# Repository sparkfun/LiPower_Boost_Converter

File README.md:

LiPower - Boost Converter
========================

[
*LiPower - Boost Converter (PRT-10255)*](https://www.sparkfun.com/products/10255)

This board is based on the TPS61200 boost converter. The board is configured to work with a LiPo battery, has a
solder jumper selectable between 5V and 3.3V output, and an under voltage protection of 2.6V. 

Repository Contents
-------------------
* **/Hardware** - All Eagle design files (.brd, .sch, .STL)
* **/Production** - Test bed files and production panel files

License Information
-------------------
The hardware is released under [Creative Commons ShareAlike 4.0 International](https://creativecommons.org/licenses/by-sa/4.0/).

Distributed as-is; no warranty is given.

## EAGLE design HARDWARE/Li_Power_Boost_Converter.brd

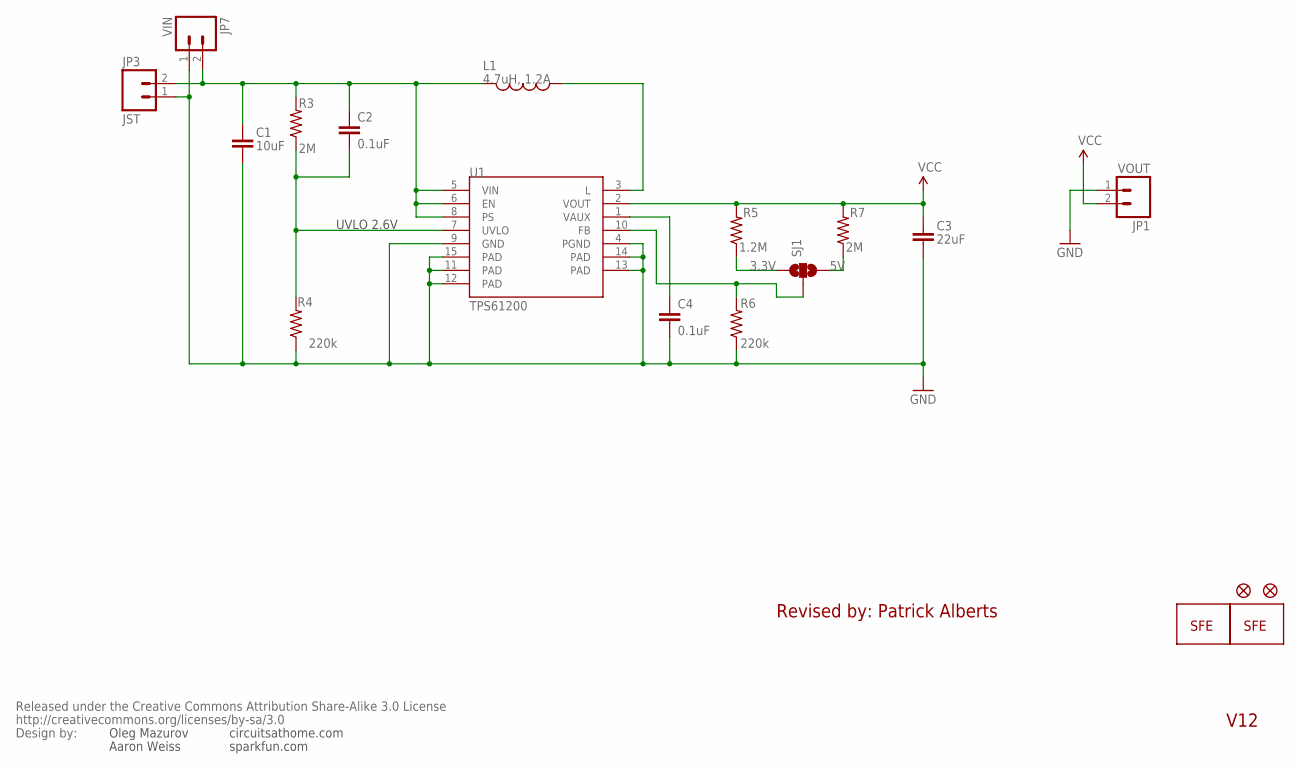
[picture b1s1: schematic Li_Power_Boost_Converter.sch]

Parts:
C1: 10uF; 1206
C2, C4: 0.1uF; 0603-CAP
C3: 22uF; 0805
JP1: VOUT; 1X02
JP2: LOGO-SFESK; SFE-LOGO-FLAME
JP3: JST; JST-2-SMD
JP4, JP5: FIDUCIAL1X2; FIDUCIAL-1X2
JP6: LOGO-SFENEW; SFE-NEW-WEBLOGO
JP7: VIN; 1X02
L1: 4.7uH, 1.2A; CDRH2D09
R3, R7: 2M; 0603-RES
R4, R6: 220k; 0603-RES
R5: 1.2M; 0603-RES
SJ1: SOLDERJUMPER_2WAYPASTE2&3; SJ_3_PASTE2&3
U1: TPS61200; QFN-10_PAD
U$1: CREATIVE_COMMONS

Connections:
3.3V: R5.1, SJ1.1
5V: R7.1, SJ1.3
FB: R6.2, SJ1.2, U1.10 (FB)
GND: C1.2, C3.2, C4.2, JP1.1, JP3.1, JP7.1, R4.1, R6.1, U1.4 (PGND), U1.9 (GND), U1.11 (PAD), U1.12 (PAD), U1.13 (PAD), U1.14 (PAD), U1.15 (PAD)
unnamed: C4.1, U1.1 (VAUX)
unnamed: L1.P$1 (1), U1.3 (L)
UVLO: C2.2, R3.1, R4.2, U1.7 (UVLO)
VCC: C3.1, JP1.2, R5.2, R7.2, U1.2 (VOUT)
VIN: C1.1, C2.1, JP3.2, JP7.2, L1.P$2 (2), R3.2, U1.5 (VIN), U1.6 (EN), U1.8 (PS)

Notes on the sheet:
UVLO 2.6V
circuitsathome.com
Oleg Mazurov
Aaron Weiss
sparkfun.com
V12
Revised by: Patrick Alberts

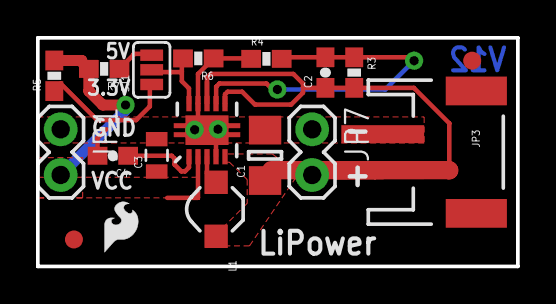
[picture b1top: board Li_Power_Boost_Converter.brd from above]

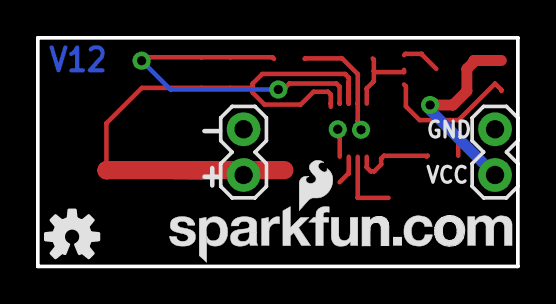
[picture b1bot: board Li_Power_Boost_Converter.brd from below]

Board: 2 copper layers, 26.7 x 12.7 mm, 21 parts (2 on the bottom side), 9 nets.

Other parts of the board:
FRAME1: FRAME-LETTER; CREATIVE_COMMONS
U$2: OSHW-LOGO-S

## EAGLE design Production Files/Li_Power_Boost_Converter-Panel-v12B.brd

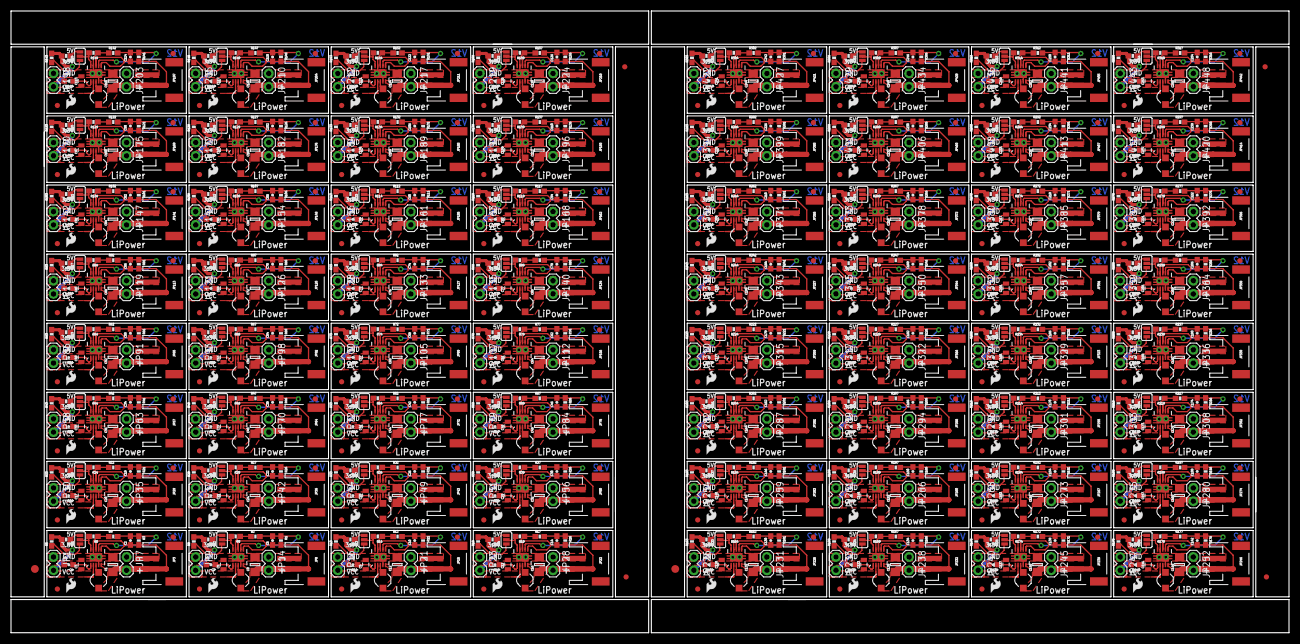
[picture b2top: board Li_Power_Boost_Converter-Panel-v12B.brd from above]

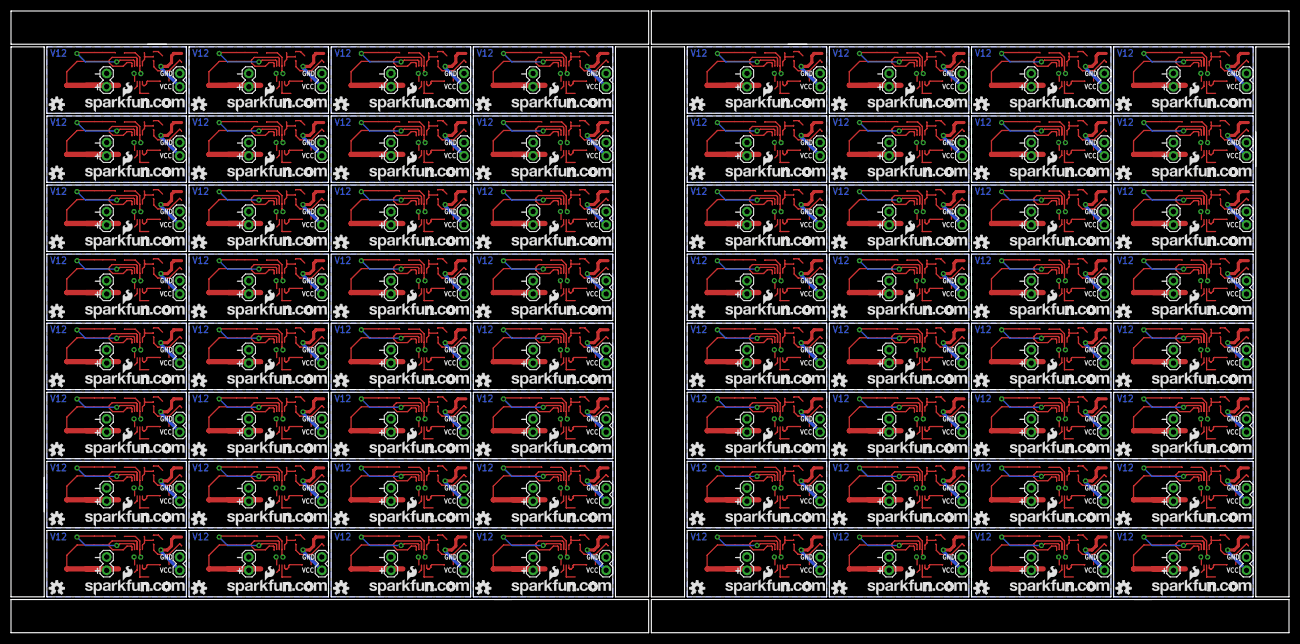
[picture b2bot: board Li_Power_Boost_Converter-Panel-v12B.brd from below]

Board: 2 copper layers, 244.3 x 118.9 mm, 1286 parts (128 on the bottom side), 576 nets.

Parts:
C1, C8, C12, C16, C20, C24, C28, C32, C36, C40, C44, C48, C52, C56, C60, C64, C68, C72, C76, C80, C84, C88, C92, C96, C100, C104, C108, C112, C116, C120, C124, C128, C132, C136, C140, C144, C148, C152, C156, C160, C164, C168, C172, C176, C180, C184, C188, C192, C196, C200, C204, C208, C212, C216, C220, C224, C228, C232, C236, C240, C244, C248, C252, C256: 10uF; 1206
C2, C4, C6, C7, C10, C11, C14, C15, C18, C19, C22, C23, C26, C27, C30, C31, C34, C35, C38, C39, C42, C43, C46, C47, C50, C51, C54, C55, C58, C59, C62, C63, C66, C67, C70, C71, C74, C75, C78, C79, C82, C83, C86, C87, C90, C91, C94, C95, C98, C99, C102, C103, C106, C107, C110, C111, C114, C115, C118, C119, C122, C123, C126, C127, C130, C131, C134, C135, C138, C139, C142, C143, C146, C147, C150, C151, C154, C155, C158, C159, C162, C163, C166, C167, C170, C171, C174, C175, C178, C179, C182, C183, C186, C187, C190, C191, C194, C195, C198, C199, C202, C203, C206, C207, C210, C211, C214, C215, C218, C219, C222, C223, C226, C227, C230, C231, C234, C235, C238, C239, C242, C243, C246, C247, C250, C251, C254, C255: 0.1uF; 0603-CAP
C3, C5, C9, C13, C17, C21, C25, C29, C33, C37, C41, C45, C49, C53, C57, C61, C65, C69, C73, C77, C81, C85, C89, C93, C97, C101, C105, C109, C113, C117, C121, C125, C129, C133, C137, C141, C145, C149, C153, C157, C161, C165, C169, C173, C177, C181, C185, C189, C193, C197, C201, C205, C209, C213, C217, C221, C225, C229, C233, C237, C241, C245, C249, C253: 22uF; 0805
E$1, E$6: FIDUCIAL-1.5X3
E$2, E$3, E$4, E$5: FIDUCIAL-1X2
JP1, JP9, JP16, JP23, JP30, JP37, JP44, JP51, JP58, JP65, JP72, JP79, JP86, JP93, JP100, JP107, JP114, JP121, JP128, JP135, JP142, JP149, JP156, JP163, JP170, JP177, JP184, JP191, JP198, JP205, JP212, JP219, JP226, JP233, JP240, JP247, JP254, JP261, JP268, JP275, JP282, JP289, JP296, JP303, JP310, JP317, JP324, JP331, JP338, JP345, JP352, JP359, JP366, JP373, JP380, JP387, JP394, JP401, JP408, JP415, JP422, JP429, JP436, JP443: VOUT; 1X02
JP2, JP10, JP17, JP24, JP31, JP38, JP45, JP52, JP59, JP66, JP73, JP80, JP87, JP94, JP101, JP108, JP115, JP122, JP129, JP136, JP143, JP150, JP157, JP164, JP171, JP178, JP185, JP192, JP199, JP206, JP213, JP220, JP227, JP234, JP241, JP248, JP255, JP262, JP269, JP276, JP283, JP290, JP297, JP304, JP311, JP318, JP325, JP332, JP339, JP346, JP353, JP360, JP367, JP374, JP381, JP388, JP395, JP402, JP409, JP416, JP423, JP430, JP437, JP444: LOGO-SFESK; SFE-LOGO-FLAME
JP3, JP8, JP15, JP22, JP29, JP36, JP43, JP50, JP57, JP64, JP71, JP78, JP85, JP92, JP99, JP106, JP113, JP120, JP127, JP134, JP141, JP148, JP155, JP162, JP169, JP176, JP183, JP190, JP197, JP204, JP211, JP218, JP225, JP232, JP239, JP246, JP253, JP260, JP267, JP274, JP281, JP288, JP295, JP302, JP309, JP316, JP323, JP330, JP337, JP344, JP351, JP358, JP365, JP372, JP379, JP386, JP393, JP400, JP407, JP414, JP421, JP428, JP435, JP442: JST; JST-2-SMD
JP4, JP5, JP11, JP12, JP18, JP19, JP25, JP26, JP32, JP33, JP39, JP40, JP46, JP47, JP53, JP54, JP60, JP61, JP67, JP68, JP74, JP75, JP81, JP82, JP88, JP89, JP95, JP96, JP102, JP103, JP109, JP110, JP116, JP117, JP123, JP124, JP130, JP131, JP137, JP138, JP144, JP145, JP151, JP152, JP158, JP159, JP165, JP166, JP172, JP173, JP179, JP180, JP186, JP187, JP193, JP194, JP200, JP201, JP207, JP208, JP214, JP215, JP221, JP222, JP228, JP229, JP235, JP236, JP242, JP243, JP249, JP250, JP256, JP257, JP263, JP264, JP270, JP271, JP277, JP278, JP284, JP285, JP291, JP292, JP298, JP299, JP305, JP306, JP312, JP313, JP319, JP320, JP326, JP327, JP333, JP334, JP340, JP341, JP347, JP348, JP354, JP355, JP361, JP362, JP368, JP369, JP375, JP376, JP382, JP383, JP389, JP390, JP396, JP397, JP403, JP404, JP410, JP411, JP417, JP418, JP424, JP425, JP431, JP432, JP438, JP439, JP445, JP446: FIDUCIAL1X2; FIDUCIAL-1X2
JP6, JP13, JP20, JP27, JP34, JP41, JP48, JP55, JP62, JP69, JP76, JP83, JP90, JP97, JP104, JP111, JP118, JP125, JP132, JP139, JP146, JP153, JP160, JP167, JP174, JP181, JP188, JP195, JP202, JP209, JP216, JP223, JP230, JP237, JP244, JP251, JP258, JP265, JP272, JP279, JP286, JP293, JP300, JP307, JP314, JP321, JP328, JP335, JP342, JP349, JP356, JP363, JP370, JP377, JP384, JP391, JP398, JP405, JP412, JP419, JP426, JP433, JP440, JP447: LOGO-SFENEW; SFE-NEW-WEBLOGO
JP7, JP14, JP21, JP28, JP35, JP42, JP49, JP56, JP63, JP70, JP77, JP84, JP91, JP98, JP105, JP112, JP119, JP126, JP133, JP140, JP147, JP154, JP161, JP168, JP175, JP182, JP189, JP196, JP203, JP210, JP217, JP224, JP231, JP238, JP245, JP252, JP259, JP266, JP273, JP280, JP287, JP294, JP301, JP308, JP315, JP322, JP329, JP336, JP343, JP350, JP357, JP364, JP371, JP378, JP385, JP392, JP399, JP406, JP413, JP420, JP427, JP434, JP441, JP448: VIN; 1X02
L1, L2, L3, L4, L5, L6, L7, L8, L9, L10, L11, L12, L13, L14, L15, L16, L17, L18, L19, L20, L21, L22, L23, L24, L25, L26, L27, L28, L29, L30, L31, L32, L33, L34, L35, L36, L37, L38, L39, L40, L41, L42, L43, L44, L45, L46, L47, L48, L49, L50, L51, L52, L53, L54, L55, L56, L57, L58, L59, L60, L61, L62, L63, L64: 4.7uH, 1.2A; CDRH2D09
R1, R3, R7, R10, R11, R15, R16, R20, R21, R25, R26, R30, R31, R35, R36, R40, R41, R45, R46, R50, R51, R55, R56, R60, R61, R65, R66, R70, R71, R75, R76, R80, R81, R85, R86, R90, R91, R95, R96, R100, R101, R105, R106, R110, R111, R115, R116, R120, R121, R125, R126, R130, R131, R135, R136, R140, R141, R145, R146, R150, R151, R155, R156, R160, R161, R165, R166, R170, R171, R175, R176, R180, R181, R185, R186, R190, R191, R195, R196, R200, R201, R205, R206, R210, R211, R215, R216, R220, R221, R225, R226, R230, R231, R235, R236, R240, R241, R245, R246, R250, R251, R255, R256, R260, R261, R265, R266, R270, R271, R275, R276, R280, R281, R285, R286, R290, R291, R295, R296, R300, R301, R305, R306, R310, R311, R315, R316, R320: 2M; 0603-RES
R2, R4, R6, R9, R12, R14, R17, R19, R22, R24, R27, R29, R32, R34, R37, R39, R42, R44, R47, R49, R52, R54, R57, R59, R62, R64, R67, R69, R72, R74, R77, R79, R82, R84, R87, R89, R92, R94, R97, R99, R102, R104, R107, R109, R112, R114, R117, R119, R122, R124, R127, R129, R132, R134, R137, R139, R142, R144, R147, R149, R152, R154, R157, R159, R162, R164, R167, R169, R172, R174, R177, R179, R182, R184, R187, R189, R192, R194, R197, R199, R202, R204, R207, R209, R212, R214, R217, R219, R222, R224, R227, R229, R232, R234, R237, R239, R242, R244, R247, R249, R252, R254, R257, R259, R262, R264, R267, R269, R272, R274, R277, R279, R282, R284, R287, R289, R292, R294, R297, R299, R302, R304, R307, R309, R312, R314, R317, R319: 220k; 0603-RES
R5, R8, R13, R18, R23, R28, R33, R38, R43, R48, R53, R58, R63, R68, R73, R78, R83, R88, R93, R98, R103, R108, R113, R118, R123, R128, R133, R138, R143, R148, R153, R158, R163, R168, R173, R178, R183, R188, R193, R198, R203, R208, R213, R218, R223, R228, R233, R238, R243, R248, R253, R258, R263, R268, R273, R278, R283, R288, R293, R298, R303, R308, R313, R318: 1.2M; 0603-RES
SJ1, SJ2, SJ3, SJ4, SJ5, SJ6, SJ7, SJ8, SJ9, SJ10, SJ11, SJ12, SJ13, SJ14, SJ15, SJ16, SJ17, SJ18, SJ19, SJ20, SJ21, SJ22, SJ23, SJ24, SJ25, SJ26, SJ27, SJ28, SJ29, SJ30, SJ31, SJ32, SJ33, SJ34, SJ35, SJ36, SJ37, SJ38, SJ39, SJ40, SJ41, SJ42, SJ43, SJ44, SJ45, SJ46, SJ47, SJ48, SJ49, SJ50, SJ51, SJ52, SJ53, SJ54, SJ55, SJ56, SJ57, SJ58, SJ59, SJ60, SJ61, SJ62, SJ63, SJ64: SJ_3_PASTE2&3
U1, U2, U3, U4, U5, U6, U7, U8, U9, U10, U11, U12, U13, U14, U15, U16, U17, U18, U19, U20, U21, U22, U23, U24, U25, U26, U27, U28, U29, U30, U31, U32, U33, U34, U35, U36, U37, U38, U39, U40, U41, U42, U43, U44, U45, U46, U47, U48, U49, U50, U51, U52, U53, U54, U55, U56, U57, U58, U59, U60, U61, U62, U63, U64: TPS61200; QFN-10_PAD
U$1, U$2, U$3, U$4, U$5, U$6, U$7, U$8, U$9, U$10, U$11, U$12, U$13, U$14, U$15, U$16, U$17, U$18, U$19, U$20, U$21, U$22, U$23, U$24, U$25, U$26, U$27, U$28, U$29, U$30, U$31, U$32, U$33, U$34, U$35, U$36, U$37, U$38, U$39, U$40, U$41, U$42, U$43, U$44, U$45, U$46, U$47, U$48, U$49, U$50, U$51, U$52, U$53, U$54, U$55, U$56, U$57, U$58, U$59, U$60, U$61, U$62, U$63, U$64: OSHW-LOGO-S

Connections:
3.3V: R5.1, SJ1.1
3.3V1: R8.1, SJ2.1
3.3V2: R13.1, SJ3.1
3.3V3: R18.1, SJ4.1
3.3V4: R23.1, SJ5.1
3.3V5: R28.1, SJ6.1
3.3V6: R33.1, SJ7.1
3.3V7: R38.1, SJ8.1
3.3V8: R43.1, SJ9.1
3.3V9: R48.1, SJ10.1
3.3V10: R53.1, SJ11.1
3.3V11: R58.1, SJ12.1
3.3V12: R63.1, SJ13.1
3.3V13: R68.1, SJ14.1
3.3V14: R73.1, SJ15.1
3.3V15: R78.1, SJ16.1
3.3V16: R83.1, SJ17.1
3.3V17: R88.1, SJ18.1
3.3V18: R93.1, SJ19.1
3.3V19: R98.1, SJ20.1
3.3V20: R103.1, SJ21.1
3.3V21: R108.1, SJ22.1
3.3V22: R113.1, SJ23.1
3.3V23: R118.1, SJ24.1
3.3V24: R123.1, SJ25.1
3.3V25: R128.1, SJ26.1
3.3V26: R133.1, SJ27.1
3.3V27: R138.1, SJ28.1
3.3V28: R143.1, SJ29.1
3.3V29: R148.1, SJ30.1
3.3V30: R153.1, SJ31.1
3.3V31: R158.1, SJ32.1
3.3V32: R163.1, SJ33.1
3.3V33: R168.1, SJ34.1
3.3V34: R173.1, SJ35.1
3.3V35: R178.1, SJ36.1
3.3V36: R183.1, SJ37.1
3.3V37: R188.1, SJ38.1
3.3V38: R193.1, SJ39.1
3.3V39: R198.1, SJ40.1
3.3V40: R203.1, SJ41.1
3.3V41: R208.1, SJ42.1
3.3V42: R213.1, SJ43.1
3.3V43: R218.1, SJ44.1
3.3V44: R223.1, SJ45.1
3.3V45: R228.1, SJ46.1
3.3V46: R233.1, SJ47.1
3.3V47: R238.1, SJ48.1
3.3V48: R243.1, SJ49.1
3.3V49: R248.1, SJ50.1
3.3V50: R253.1, SJ51.1
3.3V51: R258.1, SJ52.1
3.3V52: R263.1, SJ53.1
3.3V53: R268.1, SJ54.1
3.3V54: R273.1, SJ55.1
3.3V55: R278.1, SJ56.1
3.3V56: R283.1, SJ57.1
3.3V57: R288.1, SJ58.1
3.3V58: R293.1, SJ59.1
3.3V59: R298.1, SJ60.1
3.3V60: R303.1, SJ61.1
3.3V61: R308.1, SJ62.1
3.3V62: R313.1, SJ63.1
3.3V63: R318.1, SJ64.1
5V: R7.1, SJ1.3
5V1: R10.1, SJ2.3
5V2: R15.1, SJ3.3
5V3: R20.1, SJ4.3
5V4: R25.1, SJ5.3
5V5: R30.1, SJ6.3
5V6: R35.1, SJ7.3
5V7: R40.1, SJ8.3
5V8: R45.1, SJ9.3
5V9: R50.1, SJ10.3
5V10: R55.1, SJ11.3
5V11: R60.1, SJ12.3
5V12: R65.1, SJ13.3
5V13: R70.1, SJ14.3
5V14: R75.1, SJ15.3
5V15: R80.1, SJ16.3
5V16: R85.1, SJ17.3
5V17: R90.1, SJ18.3
5V18: R95.1, SJ19.3
5V19: R100.1, SJ20.3
5V20: R105.1, SJ21.3
5V21: R110.1, SJ22.3
5V22: R115.1, SJ23.3
5V23: R120.1, SJ24.3
5V24: R125.1, SJ25.3
5V25: R130.1, SJ26.3
5V26: R135.1, SJ27.3
5V27: R140.1, SJ28.3
5V28: R145.1, SJ29.3
5V29: R150.1, SJ30.3
5V30: R155.1, SJ31.3
5V31: R160.1, SJ32.3
5V32: R165.1, SJ33.3
5V33: R170.1, SJ34.3
5V34: R175.1, SJ35.3
5V35: R180.1, SJ36.3
5V36: R185.1, SJ37.3
5V37: R190.1, SJ38.3
5V38: R195.1, SJ39.3
5V39: R200.1, SJ40.3
5V40: R205.1, SJ41.3
5V41: R210.1, SJ42.3
5V42: R215.1, SJ43.3
5V43: R220.1, SJ44.3
5V44: R225.1, SJ45.3
5V45: R230.1, SJ46.3
5V46: R235.1, SJ47.3
5V47: R240.1, SJ48.3
5V48: R245.1, SJ49.3
5V49: R250.1, SJ50.3
5V50: R255.1, SJ51.3
5V51: R260.1, SJ52.3
5V52: R265.1, SJ53.3
5V53: R270.1, SJ54.3
5V54: R275.1, SJ55.3
5V55: R280.1, SJ56.3
5V56: R285.1, SJ57.3
5V57: R290.1, SJ58.3
5V58: R295.1, SJ59.3
5V59: R300.1, SJ60.3
5V60: R305.1, SJ61.3
5V61: R310.1, SJ62.3
5V62: R315.1, SJ63.3
5V63: R320.1, SJ64.3
FB: R6.2, SJ1.2, U1.10
FB1: R9.2, SJ2.2, U2.10
FB2: R14.2, SJ3.2, U3.10
FB3: R19.2, SJ4.2, U4.10
FB4: R24.2, SJ5.2, U5.10
FB5: R29.2, SJ6.2, U6.10
FB6: R34.2, SJ7.2, U7.10
FB7: R39.2, SJ8.2, U8.10
FB8: R44.2, SJ9.2, U9.10
FB9: R49.2, SJ10.2, U10.10
FB10: R54.2, SJ11.2, U11.10
FB11: R59.2, SJ12.2, U12.10
FB12: R64.2, SJ13.2, U13.10
FB13: R69.2, SJ14.2, U14.10
FB14: R74.2, SJ15.2, U15.10
FB15: R79.2, SJ16.2, U16.10
FB16: R84.2, SJ17.2, U17.10
FB17: R89.2, SJ18.2, U18.10
FB18: R94.2, SJ19.2, U19.10
FB19: R99.2, SJ20.2, U20.10
FB20: R104.2, SJ21.2, U21.10
FB21: R109.2, SJ22.2, U22.10
FB22: R114.2, SJ23.2, U23.10
FB23: R119.2, SJ24.2, U24.10
FB24: R124.2, SJ25.2, U25.10
FB25: R129.2, SJ26.2, U26.10
FB26: R134.2, SJ27.2, U27.10
FB27: R139.2, SJ28.2, U28.10
FB28: R144.2, SJ29.2, U29.10
FB29: R149.2, SJ30.2, U30.10
FB30: R154.2, SJ31.2, U31.10
FB31: R159.2, SJ32.2, U32.10
FB32: R164.2, SJ33.2, U33.10
FB33: R169.2, SJ34.2, U34.10
FB34: R174.2, SJ35.2, U35.10
FB35: R179.2, SJ36.2, U36.10
FB36: R184.2, SJ37.2, U37.10
FB37: R189.2, SJ38.2, U38.10
FB38: R194.2, SJ39.2, U39.10
FB39: R199.2, SJ40.2, U40.10
FB40: R204.2, SJ41.2, U41.10
FB41: R209.2, SJ42.2, U42.10
FB42: R214.2, SJ43.2, U43.10
FB43: R219.2, SJ44.2, U44.10
FB44: R224.2, SJ45.2, U45.10
FB45: R229.2, SJ46.2, U46.10
FB46: R234.2, SJ47.2, U47.10
FB47: R239.2, SJ48.2, U48.10
FB48: R244.2, SJ49.2, U49.10
FB49: R249.2, SJ50.2, U50.10
FB50: R254.2, SJ51.2, U51.10
FB51: R259.2, SJ52.2, U52.10
FB52: R264.2, SJ53.2, U53.10
FB53: R269.2, SJ54.2, U54.10
FB54: R274.2, SJ55.2, U55.10
FB55: R279.2, SJ56.2, U56.10
FB56: R284.2, SJ57.2, U57.10
FB57: R289.2, SJ58.2, U58.10
FB58: R294.2, SJ59.2, U59.10
FB59: R299.2, SJ60.2, U60.10
FB60: R304.2, SJ61.2, U61.10
FB61: R309.2, SJ62.2, U62.10
FB62: R314.2, SJ63.2, U63.10
FB63: R319.2, SJ64.2, U64.10
GND: C1.2, C3.2, C4.2, JP1.1, JP3.1, JP7.1, R4.1, R6.1, U1.4, U1.9, U1.11, U1.12, U1.13, U1.14, U1.15
GND1: C5.2, C7.2, C8.2, JP8.1, JP9.1, JP14.1, R2.1, R9.1, U2.4, U2.9, U2.11, U2.12, U2.13, U2.14, U2.15
GND2: C9.2, C11.2, C12.2, JP15.1, JP16.1, JP21.1, R12.1, R14.1, U3.4, U3.9, U3.11, U3.12, U3.13, U3.14, U3.15
GND3: C13.2, C15.2, C16.2, JP22.1, JP23.1, JP28.1, R17.1, R19.1, U4.4, U4.9, U4.11, U4.12, U4.13, U4.14, U4.15
GND4: C17.2, C19.2, C20.2, JP29.1, JP30.1, JP35.1, R22.1, R24.1, U5.4, U5.9, U5.11, U5.12, U5.13, U5.14, U5.15
GND5: C21.2, C23.2, C24.2, JP36.1, JP37.1, JP42.1, R27.1, R29.1, U6.4, U6.9, U6.11, U6.12, U6.13, U6.14, U6.15
GND6: C25.2, C27.2, C28.2, JP43.1, JP44.1, JP49.1, R32.1, R34.1, U7.4, U7.9, U7.11, U7.12, U7.13, U7.14, U7.15
GND7: C29.2, C31.2, C32.2, JP50.1, JP51.1, JP56.1, R37.1, R39.1, U8.4, U8.9, U8.11, U8.12, U8.13, U8.14, U8.15
GND8: C33.2, C35.2, C36.2, JP57.1, JP58.1, JP63.1, R42.1, R44.1, U9.4, U9.9, U9.11, U9.12, U9.13, U9.14, U9.15
GND9: C37.2, C39.2, C40.2, JP64.1, JP65.1, JP70.1, R47.1, R49.1, U10.4, U10.9, U10.11, U10.12, U10.13, U10.14, U10.15
GND10: C41.2, C43.2, C44.2, JP71.1, JP72.1, JP77.1, R52.1, R54.1, U11.4, U11.9, U11.11, U11.12, U11.13, U11.14, U11.15
GND11: C45.2, C47.2, C48.2, JP78.1, JP79.1, JP84.1, R57.1, R59.1, U12.4, U12.9, U12.11, U12.12, U12.13, U12.14, U12.15
GND12: C49.2, C51.2, C52.2, JP85.1, JP86.1, JP91.1, R62.1, R64.1, U13.4, U13.9, U13.11, U13.12, U13.13, U13.14, U13.15
GND13: C53.2, C55.2, C56.2, JP92.1, JP93.1, JP98.1, R67.1, R69.1, U14.4, U14.9, U14.11, U14.12, U14.13, U14.14, U14.15
GND14: C57.2, C59.2, C60.2, JP99.1, JP100.1, JP105.1, R72.1, R74.1, U15.4, U15.9, U15.11, U15.12, U15.13, U15.14, U15.15
GND15: C61.2, C63.2, C64.2, JP106.1, JP107.1, JP112.1, R77.1, R79.1, U16.4, U16.9, U16.11, U16.12, U16.13, U16.14, U16.15
GND16: C65.2, C67.2, C68.2, JP113.1, JP114.1, JP119.1, R82.1, R84.1, U17.4, U17.9, U17.11, U17.12, U17.13, U17.14, U17.15
GND17: C69.2, C71.2, C72.2, JP120.1, JP121.1, JP126.1, R87.1, R89.1, U18.4, U18.9, U18.11, U18.12, U18.13, U18.14, U18.15
GND18: C73.2, C75.2, C76.2, JP127.1, JP128.1, JP133.1, R92.1, R94.1, U19.4, U19.9, U19.11, U19.12, U19.13, U19.14, U19.15
GND19: C77.2, C79.2, C80.2, JP134.1, JP135.1, JP140.1, R97.1, R99.1, U20.4, U20.9, U20.11, U20.12, U20.13, U20.14, U20.15
GND20: C81.2, C83.2, C84.2, JP141.1, JP142.1, JP147.1, R102.1, R104.1, U21.4, U21.9, U21.11, U21.12, U21.13, U21.14, U21.15
GND21: C85.2, C87.2, C88.2, JP148.1, JP149.1, JP154.1, R107.1, R109.1, U22.4, U22.9, U22.11, U22.12, U22.13, U22.14, U22.15
GND22: C89.2, C91.2, C92.2, JP155.1, JP156.1, JP161.1, R112.1, R114.1, U23.4, U23.9, U23.11, U23.12, U23.13, U23.14, U23.15
GND23: C93.2, C95.2, C96.2, JP162.1, JP163.1, JP168.1, R117.1, R119.1, U24.4, U24.9, U24.11, U24.12, U24.13, U24.14, U24.15
GND24: C97.2, C99.2, C100.2, JP169.1, JP170.1, JP175.1, R122.1, R124.1, U25.4, U25.9, U25.11, U25.12, U25.13, U25.14, U25.15
GND25: C101.2, C103.2, C104.2, JP176.1, JP177.1, JP182.1, R127.1, R129.1, U26.4, U26.9, U26.11, U26.12, U26.13, U26.14, U26.15
GND26: C105.2, C107.2, C108.2, JP183.1, JP184.1, JP189.1, R132.1, R134.1, U27.4, U27.9, U27.11, U27.12, U27.13, U27.14, U27.15
GND27: C109.2, C111.2, C112.2, JP190.1, JP191.1, JP196.1, R137.1, R139.1, U28.4, U28.9, U28.11, U28.12, U28.13, U28.14, U28.15
GND28: C113.2, C115.2, C116.2, JP197.1, JP198.1, JP203.1, R142.1, R144.1, U29.4, U29.9, U29.11, U29.12, U29.13, U29.14, U29.15
GND29: C117.2, C119.2, C120.2, JP204.1, JP205.1, JP210.1, R147.1, R149.1, U30.4, U30.9, U30.11, U30.12, U30.13, U30.14, U30.15
GND30: C121.2, C123.2, C124.2, JP211.1, JP212.1, JP217.1, R152.1, R154.1, U31.4, U31.9, U31.11, U31.12, U31.13, U31.14, U31.15
GND31: C125.2, C127.2, C128.2, JP218.1, JP219.1, JP224.1, R157.1, R159.1, U32.4, U32.9, U32.11, U32.12, U32.13, U32.14, U32.15
GND32: C129.2, C131.2, C132.2, JP225.1, JP226.1, JP231.1, R162.1, R164.1, U33.4, U33.9, U33.11, U33.12, U33.13, U33.14, U33.15
GND33: C133.2, C135.2, C136.2, JP232.1, JP233.1, JP238.1, R167.1, R169.1, U34.4, U34.9, U34.11, U34.12, U34.13, U34.14, U34.15
GND34: C137.2, C139.2, C140.2, JP239.1, JP240.1, JP245.1, R172.1, R174.1, U35.4, U35.9, U35.11, U35.12, U35.13, U35.14, U35.15
GND35: C141.2, C143.2, C144.2, JP246.1, JP247.1, JP252.1, R177.1, R179.1, U36.4, U36.9, U36.11, U36.12, U36.13, U36.14, U36.15
GND36: C145.2, C147.2, C148.2, JP253.1, JP254.1, JP259.1, R182.1, R184.1, U37.4, U37.9, U37.11, U37.12, U37.13, U37.14, U37.15
GND37: C149.2, C151.2, C152.2, JP260.1, JP261.1, JP266.1, R187.1, R189.1, U38.4, U38.9, U38.11, U38.12, U38.13, U38.14, U38.15
GND38: C153.2, C155.2, C156.2, JP267.1, JP268.1, JP273.1, R192.1, R194.1, U39.4, U39.9, U39.11, U39.12, U39.13, U39.14, U39.15
GND39: C157.2, C159.2, C160.2, JP274.1, JP275.1, JP280.1, R197.1, R199.1, U40.4, U40.9, U40.11, U40.12, U40.13, U40.14, U40.15
GND40: C161.2, C163.2, C164.2, JP281.1, JP282.1, JP287.1, R202.1, R204.1, U41.4, U41.9, U41.11, U41.12, U41.13, U41.14, U41.15
GND41: C165.2, C167.2, C168.2, JP288.1, JP289.1, JP294.1, R207.1, R209.1, U42.4, U42.9, U42.11, U42.12, U42.13, U42.14, U42.15
GND42: C169.2, C171.2, C172.2, JP295.1, JP296.1, JP301.1, R212.1, R214.1, U43.4, U43.9, U43.11, U43.12, U43.13, U43.14, U43.15
GND43: C173.2, C175.2, C176.2, JP302.1, JP303.1, JP308.1, R217.1, R219.1, U44.4, U44.9, U44.11, U44.12, U44.13, U44.14, U44.15
GND44: C177.2, C179.2, C180.2, JP309.1, JP310.1, JP315.1, R222.1, R224.1, U45.4, U45.9, U45.11, U45.12, U45.13, U45.14, U45.15
GND45: C181.2, C183.2, C184.2, JP316.1, JP317.1, JP322.1, R227.1, R229.1, U46.4, U46.9, U46.11, U46.12, U46.13, U46.14, U46.15
GND46: C185.2, C187.2, C188.2, JP323.1, JP324.1, JP329.1, R232.1, R234.1, U47.4, U47.9, U47.11, U47.12, U47.13, U47.14, U47.15
GND47: C189.2, C191.2, C192.2, JP330.1, JP331.1, JP336.1, R237.1, R239.1, U48.4, U48.9, U48.11, U48.12, U48.13, U48.14, U48.15
GND48: C193.2, C195.2, C196.2, JP337.1, JP338.1, JP343.1, R242.1, R244.1, U49.4, U49.9, U49.11, U49.12, U49.13, U49.14, U49.15
GND49: C197.2, C199.2, C200.2, JP344.1, JP345.1, JP350.1, R247.1, R249.1, U50.4, U50.9, U50.11, U50.12, U50.13, U50.14, U50.15
GND50: C201.2, C203.2, C204.2, JP351.1, JP352.1, JP357.1, R252.1, R254.1, U51.4, U51.9, U51.11, U51.12, U51.13, U51.14, U51.15
GND51: C205.2, C207.2, C208.2, JP358.1, JP359.1, JP364.1, R257.1, R259.1, U52.4, U52.9, U52.11, U52.12, U52.13, U52.14, U52.15
GND52: C209.2, C211.2, C212.2, JP365.1, JP366.1, JP371.1, R262.1, R264.1, U53.4, U53.9, U53.11, U53.12, U53.13, U53.14, U53.15
GND53: C213.2, C215.2, C216.2, JP372.1, JP373.1, JP378.1, R267.1, R269.1, U54.4, U54.9, U54.11, U54.12, U54.13, U54.14, U54.15
GND54: C217.2, C219.2, C220.2, JP379.1, JP380.1, JP385.1, R272.1, R274.1, U55.4, U55.9, U55.11, U55.12, U55.13, U55.14, U55.15
GND55: C221.2, C223.2, C224.2, JP386.1, JP387.1, JP392.1, R277.1, R279.1, U56.4, U56.9, U56.11, U56.12, U56.13, U56.14, U56.15
GND56: C225.2, C227.2, C228.2, JP393.1, JP394.1, JP399.1, R282.1, R284.1, U57.4, U57.9, U57.11, U57.12, U57.13, U57.14, U57.15
GND57: C229.2, C231.2, C232.2, JP400.1, JP401.1, JP406.1, R287.1, R289.1, U58.4, U58.9, U58.11, U58.12, U58.13, U58.14, U58.15
GND58: C233.2, C235.2, C236.2, JP407.1, JP408.1, JP413.1, R292.1, R294.1, U59.4, U59.9, U59.11, U59.12, U59.13, U59.14, U59.15
GND59: C237.2, C239.2, C240.2, JP414.1, JP415.1, JP420.1, R297.1, R299.1, U60.4, U60.9, U60.11, U60.12, U60.13, U60.14, U60.15
GND60: C241.2, C243.2, C244.2, JP421.1, JP422.1, JP427.1, R302.1, R304.1, U61.4, U61.9, U61.11, U61.12, U61.13, U61.14, U61.15
GND61: C245.2, C247.2, C248.2, JP428.1, JP429.1, JP434.1, R307.1, R309.1, U62.4, U62.9, U62.11, U62.12, U62.13, U62.14, U62.15
GND62: C249.2, C251.2, C252.2, JP435.1, JP436.1, JP441.1, R312.1, R314.1, U63.4, U63.9, U63.11, U63.12, U63.13, U63.14, U63.15
GND63: C253.2, C255.2, C256.2, JP442.1, JP443.1, JP448.1, R317.1, R319.1, U64.4, U64.9, U64.11, U64.12, U64.13, U64.14, U64.15
unnamed: C4.1, U1.1
unnamed: L1.P$1, U1.3
unnamed: L2.P$1, U2.3
unnamed: C7.1, U2.1
unnamed: L3.P$1, U3.3
unnamed: C11.1, U3.1
unnamed: L4.P$1, U4.3
unnamed: C15.1, U4.1
unnamed: L5.P$1, U5.3
unnamed: C19.1, U5.1
unnamed: L6.P$1, U6.3
unnamed: C23.1, U6.1
unnamed: L7.P$1, U7.3
unnamed: C27.1, U7.1
unnamed: L8.P$1, U8.3
unnamed: C31.1, U8.1
unnamed: L9.P$1, U9.3
unnamed: C35.1, U9.1
unnamed: L10.P$1, U10.3
unnamed: C39.1, U10.1
unnamed: L11.P$1, U11.3
unnamed: C43.1, U11.1
unnamed: L12.P$1, U12.3
unnamed: C47.1, U12.1
unnamed: L13.P$1, U13.3
unnamed: C51.1, U13.1
unnamed: L14.P$1, U14.3
unnamed: C55.1, U14.1
unnamed: L15.P$1, U15.3
unnamed: C59.1, U15.1
unnamed: L16.P$1, U16.3
unnamed: C63.1, U16.1
unnamed: L17.P$1, U17.3
unnamed: C67.1, U17.1
unnamed: L18.P$1, U18.3
unnamed: C71.1, U18.1
unnamed: L19.P$1, U19.3
unnamed: C75.1, U19.1
unnamed: L20.P$1, U20.3
unnamed: C79.1, U20.1
unnamed: L21.P$1, U21.3
unnamed: C83.1, U21.1
unnamed: L22.P$1, U22.3
unnamed: C87.1, U22.1
unnamed: L23.P$1, U23.3
unnamed: C91.1, U23.1
unnamed: L24.P$1, U24.3
unnamed: C95.1, U24.1
unnamed: L25.P$1, U25.3
unnamed: C99.1, U25.1
unnamed: L26.P$1, U26.3
unnamed: C103.1, U26.1
unnamed: L27.P$1, U27.3
unnamed: C107.1, U27.1
unnamed: L28.P$1, U28.3
unnamed: C111.1, U28.1
unnamed: L29.P$1, U29.3
unnamed: C115.1, U29.1
unnamed: L30.P$1, U30.3
unnamed: C119.1, U30.1
unnamed: L31.P$1, U31.3
unnamed: C123.1, U31.1
unnamed: L32.P$1, U32.3
unnamed: C127.1, U32.1
unnamed: L33.P$1, U33.3
unnamed: C131.1, U33.1
unnamed: L34.P$1, U34.3
unnamed: C135.1, U34.1
unnamed: L35.P$1, U35.3
unnamed: C139.1, U35.1
unnamed: L36.P$1, U36.3
unnamed: C143.1, U36.1
unnamed: L37.P$1, U37.3
unnamed: C147.1, U37.1
unnamed: L38.P$1, U38.3
unnamed: C151.1, U38.1
unnamed: L39.P$1, U39.3
unnamed: C155.1, U39.1
unnamed: L40.P$1, U40.3
unnamed: C159.1, U40.1
unnamed: L41.P$1, U41.3
unnamed: C163.1, U41.1
unnamed: L42.P$1, U42.3
unnamed: C167.1, U42.1
unnamed: L43.P$1, U43.3
unnamed: C171.1, U43.1
unnamed: L44.P$1, U44.3
unnamed: C175.1, U44.1
unnamed: L45.P$1, U45.3
unnamed: C179.1, U45.1
unnamed: L46.P$1, U46.3
unnamed: C183.1, U46.1
unnamed: L47.P$1, U47.3
unnamed: C187.1, U47.1
unnamed: L48.P$1, U48.3
unnamed: C191.1, U48.1
unnamed: L49.P$1, U49.3
unnamed: C195.1, U49.1
unnamed: L50.P$1, U50.3
unnamed: C199.1, U50.1
unnamed: L51.P$1, U51.3
unnamed: C203.1, U51.1
unnamed: L52.P$1, U52.3
unnamed: C207.1, U52.1
unnamed: L53.P$1, U53.3
unnamed: C211.1, U53.1
unnamed: L54.P$1, U54.3
unnamed: C215.1, U54.1
unnamed: L55.P$1, U55.3
unnamed: C219.1, U55.1
unnamed: L56.P$1, U56.3
unnamed: C223.1, U56.1
unnamed: L57.P$1, U57.3
unnamed: C227.1, U57.1
unnamed: L58.P$1, U58.3
unnamed: C231.1, U58.1
unnamed: L59.P$1, U59.3
unnamed: C235.1, U59.1
unnamed: L60.P$1, U60.3
unnamed: C239.1, U60.1
unnamed: L61.P$1, U61.3
unnamed: C243.1, U61.1
unnamed: L62.P$1, U62.3
unnamed: C247.1, U62.1
unnamed: L63.P$1, U63.3
unnamed: C251.1, U63.1
unnamed: L64.P$1, U64.3
unnamed: C255.1, U64.1
UVLO: C2.2, R3.1, R4.2, U1.7
UVLO1: C6.2, R1.1, R2.2, U2.7
UVLO2: C10.2, R11.1, R12.2, U3.7
UVLO3: C14.2, R16.1, R17.2, U4.7
UVLO4: C18.2, R21.1, R22.2, U5.7
UVLO5: C22.2, R26.1, R27.2, U6.7
UVLO6: C26.2, R31.1, R32.2, U7.7
UVLO7: C30.2, R36.1, R37.2, U8.7
UVLO8: C34.2, R41.1, R42.2, U9.7
UVLO9: C38.2, R46.1, R47.2, U10.7
UVLO10: C42.2, R51.1, R52.2, U11.7
UVLO11: C46.2, R56.1, R57.2, U12.7
UVLO12: C50.2, R61.1, R62.2, U13.7
UVLO13: C54.2, R66.1, R67.2, U14.7
UVLO14: C58.2, R71.1, R72.2, U15.7
UVLO15: C62.2, R76.1, R77.2, U16.7
UVLO16: C66.2, R81.1, R82.2, U17.7
UVLO17: C70.2, R86.1, R87.2, U18.7
UVLO18: C74.2, R91.1, R92.2, U19.7
UVLO19: C78.2, R96.1, R97.2, U20.7
UVLO20: C82.2, R101.1, R102.2, U21.7
UVLO21: C86.2, R106.1, R107.2, U22.7
UVLO22: C90.2, R111.1, R112.2, U23.7
UVLO23: C94.2, R116.1, R117.2, U24.7
UVLO24: C98.2, R121.1, R122.2, U25.7
UVLO25: C102.2, R126.1, R127.2, U26.7
UVLO26: C106.2, R131.1, R132.2, U27.7
UVLO27: C110.2, R136.1, R137.2, U28.7
UVLO28: C114.2, R141.1, R142.2, U29.7
UVLO29: C118.2, R146.1, R147.2, U30.7
UVLO30: C122.2, R151.1, R152.2, U31.7
UVLO31: C126.2, R156.1, R157.2, U32.7
UVLO32: C130.2, R161.1, R162.2, U33.7
UVLO33: C134.2, R166.1, R167.2, U34.7
UVLO34: C138.2, R171.1, R172.2, U35.7
UVLO35: C142.2, R176.1, R177.2, U36.7
UVLO36: C146.2, R181.1, R182.2, U37.7
UVLO37: C150.2, R186.1, R187.2, U38.7
UVLO38: C154.2, R191.1, R192.2, U39.7
UVLO39: C158.2, R196.1, R197.2, U40.7
UVLO40: C162.2, R201.1, R202.2, U41.7
UVLO41: C166.2, R206.1, R207.2, U42.7
UVLO42: C170.2, R211.1, R212.2, U43.7
UVLO43: C174.2, R216.1, R217.2, U44.7
UVLO44: C178.2, R221.1, R222.2, U45.7
UVLO45: C182.2, R226.1, R227.2, U46.7
UVLO46: C186.2, R231.1, R232.2, U47.7
UVLO47: C190.2, R236.1, R237.2, U48.7
UVLO48: C194.2, R241.1, R242.2, U49.7
UVLO49: C198.2, R246.1, R247.2, U50.7
UVLO50: C202.2, R251.1, R252.2, U51.7
UVLO51: C206.2, R256.1, R257.2, U52.7
UVLO52: C210.2, R261.1, R262.2, U53.7
UVLO53: C214.2, R266.1, R267.2, U54.7
UVLO54: C218.2, R271.1, R272.2, U55.7
UVLO55: C222.2, R276.1, R277.2, U56.7
UVLO56: C226.2, R281.1, R282.2, U57.7
UVLO57: C230.2, R286.1, R287.2, U58.7
UVLO58: C234.2, R291.1, R292.2, U59.7
UVLO59: C238.2, R296.1, R297.2, U60.7
UVLO60: C242.2, R301.1, R302.2, U61.7
UVLO61: C246.2, R306.1, R307.2, U62.7
UVLO62: C250.2, R311.1, R312.2, U63.7
UVLO63: C254.2, R316.1, R317.2, U64.7
VCC: C3.1, JP1.2, R5.2, R7.2, U1.2
VCC1: C5.1, JP9.2, R8.2, R10.2, U2.2
VCC2: C9.1, JP16.2, R13.2, R15.2, U3.2
VCC3: C13.1, JP23.2, R18.2, R20.2, U4.2
VCC4: C17.1, JP30.2, R23.2, R25.2, U5.2
VCC5: C21.1, JP37.2, R28.2, R30.2, U6.2
VCC6: C25.1, JP44.2, R33.2, R35.2, U7.2
VCC7: C29.1, JP51.2, R38.2, R40.2, U8.2
VCC8: C33.1, JP58.2, R43.2, R45.2, U9.2
VCC9: C37.1, JP65.2, R48.2, R50.2, U10.2
VCC10: C41.1, JP72.2, R53.2, R55.2, U11.2
VCC11: C45.1, JP79.2, R58.2, R60.2, U12.2
VCC12: C49.1, JP86.2, R63.2, R65.2, U13.2
VCC13: C53.1, JP93.2, R68.2, R70.2, U14.2
VCC14: C57.1, JP100.2, R73.2, R75.2, U15.2
VCC15: C61.1, JP107.2, R78.2, R80.2, U16.2
VCC16: C65.1, JP114.2, R83.2, R85.2, U17.2
VCC17: C69.1, JP121.2, R88.2, R90.2, U18.2
VCC18: C73.1, JP128.2, R93.2, R95.2, U19.2
VCC19: C77.1, JP135.2, R98.2, R100.2, U20.2
VCC20: C81.1, JP142.2, R103.2, R105.2, U21.2
VCC21: C85.1, JP149.2, R108.2, R110.2, U22.2
VCC22: C89.1, JP156.2, R113.2, R115.2, U23.2
VCC23: C93.1, JP163.2, R118.2, R120.2, U24.2
VCC24: C97.1, JP170.2, R123.2, R125.2, U25.2
VCC25: C101.1, JP177.2, R128.2, R130.2, U26.2
VCC26: C105.1, JP184.2, R133.2, R135.2, U27.2
VCC27: C109.1, JP191.2, R138.2, R140.2, U28.2
VCC28: C113.1, JP198.2, R143.2, R145.2, U29.2
VCC29: C117.1, JP205.2, R148.2, R150.2, U30.2
VCC30: C121.1, JP212.2, R153.2, R155.2, U31.2
VCC31: C125.1, JP219.2, R158.2, R160.2, U32.2
VCC32: C129.1, JP226.2, R163.2, R165.2, U33.2
VCC33: C133.1, JP233.2, R168.2, R170.2, U34.2
VCC34: C137.1, JP240.2, R173.2, R175.2, U35.2
VCC35: C141.1, JP247.2, R178.2, R180.2, U36.2
VCC36: C145.1, JP254.2, R183.2, R185.2, U37.2
VCC37: C149.1, JP261.2, R188.2, R190.2, U38.2
VCC38: C153.1, JP268.2, R193.2, R195.2, U39.2
VCC39: C157.1, JP275.2, R198.2, R200.2, U40.2
VCC40: C161.1, JP282.2, R203.2, R205.2, U41.2
VCC41: C165.1, JP289.2, R208.2, R210.2, U42.2
VCC42: C169.1, JP296.2, R213.2, R215.2, U43.2
VCC43: C173.1, JP303.2, R218.2, R220.2, U44.2
VCC44: C177.1, JP310.2, R223.2, R225.2, U45.2
VCC45: C181.1, JP317.2, R228.2, R230.2, U46.2
VCC46: C185.1, JP324.2, R233.2, R235.2, U47.2
VCC47: C189.1, JP331.2, R238.2, R240.2, U48.2
VCC48: C193.1, JP338.2, R243.2, R245.2, U49.2
VCC49: C197.1, JP345.2, R248.2, R250.2, U50.2
VCC50: C201.1, JP352.2, R253.2, R255.2, U51.2
VCC51: C205.1, JP359.2, R258.2, R260.2, U52.2
VCC52: C209.1, JP366.2, R263.2, R265.2, U53.2
VCC53: C213.1, JP373.2, R268.2, R270.2, U54.2
VCC54: C217.1, JP380.2, R273.2, R275.2, U55.2
VCC55: C221.1, JP387.2, R278.2, R280.2, U56.2
VCC56: C225.1, JP394.2, R283.2, R285.2, U57.2
VCC57: C229.1, JP401.2, R288.2, R290.2, U58.2
VCC58: C233.1, JP408.2, R293.2, R295.2, U59.2
VCC59: C237.1, JP415.2, R298.2, R300.2, U60.2
VCC60: C241.1, JP422.2, R303.2, R305.2, U61.2
VCC61: C245.1, JP429.2, R308.2, R310.2, U62.2
VCC62: C249.1, JP436.2, R313.2, R315.2, U63.2
VCC63: C253.1, JP443.2, R318.2, R320.2, U64.2
VIN: C1.1, C2.1, JP3.2, JP7.2, L1.P$2, R3.2, U1.5, U1.6, U1.8
VIN1: C6.1, C8.1, JP8.2, JP14.2, L2.P$2, R1.2, U2.5, U2.6, U2.8
VIN2: C10.1, C12.1, JP15.2, JP21.2, L3.P$2, R11.2, U3.5, U3.6, U3.8
VIN3: C14.1, C16.1, JP22.2, JP28.2, L4.P$2, R16.2, U4.5, U4.6, U4.8
VIN4: C18.1, C20.1, JP29.2, JP35.2, L5.P$2, R21.2, U5.5, U5.6, U5.8
VIN5: C22.1, C24.1, JP36.2, JP42.2, L6.P$2, R26.2, U6.5, U6.6, U6.8
VIN6: C26.1, C28.1, JP43.2, JP49.2, L7.P$2, R31.2, U7.5, U7.6, U7.8
VIN7: C30.1, C32.1, JP50.2, JP56.2, L8.P$2, R36.2, U8.5, U8.6, U8.8
VIN8: C34.1, C36.1, JP57.2, JP63.2, L9.P$2, R41.2, U9.5, U9.6, U9.8
VIN9: C38.1, C40.1, JP64.2, JP70.2, L10.P$2, R46.2, U10.5, U10.6, U10.8
VIN10: C42.1, C44.1, JP71.2, JP77.2, L11.P$2, R51.2, U11.5, U11.6, U11.8
VIN11: C46.1, C48.1, JP78.2, JP84.2, L12.P$2, R56.2, U12.5, U12.6, U12.8
VIN12: C50.1, C52.1, JP85.2, JP91.2, L13.P$2, R61.2, U13.5, U13.6, U13.8
VIN13: C54.1, C56.1, JP92.2, JP98.2, L14.P$2, R66.2, U14.5, U14.6, U14.8
VIN14: C58.1, C60.1, JP99.2, JP105.2, L15.P$2, R71.2, U15.5, U15.6, U15.8
VIN15: C62.1, C64.1, JP106.2, JP112.2, L16.P$2, R76.2, U16.5, U16.6, U16.8
VIN16: C66.1, C68.1, JP113.2, JP119.2, L17.P$2, R81.2, U17.5, U17.6, U17.8
VIN17: C70.1, C72.1, JP120.2, JP126.2, L18.P$2, R86.2, U18.5, U18.6, U18.8
VIN18: C74.1, C76.1, JP127.2, JP133.2, L19.P$2, R91.2, U19.5, U19.6, U19.8
VIN19: C78.1, C80.1, JP134.2, JP140.2, L20.P$2, R96.2, U20.5, U20.6, U20.8
VIN20: C82.1, C84.1, JP141.2, JP147.2, L21.P$2, R101.2, U21.5, U21.6, U21.8
VIN21: C86.1, C88.1, JP148.2, JP154.2, L22.P$2, R106.2, U22.5, U22.6, U22.8
VIN22: C90.1, C92.1, JP155.2, JP161.2, L23.P$2, R111.2, U23.5, U23.6, U23.8
VIN23: C94.1, C96.1, JP162.2, JP168.2, L24.P$2, R116.2, U24.5, U24.6, U24.8
VIN24: C98.1, C100.1, JP169.2, JP175.2, L25.P$2, R121.2, U25.5, U25.6, U25.8
VIN25: C102.1, C104.1, JP176.2, JP182.2, L26.P$2, R126.2, U26.5, U26.6, U26.8
VIN26: C106.1, C108.1, JP183.2, JP189.2, L27.P$2, R131.2, U27.5, U27.6, U27.8
VIN27: C110.1, C112.1, JP190.2, JP196.2, L28.P$2, R136.2, U28.5, U28.6, U28.8
VIN28: C114.1, C116.1, JP197.2, JP203.2, L29.P$2, R141.2, U29.5, U29.6, U29.8
VIN29: C118.1, C120.1, JP204.2, JP210.2, L30.P$2, R146.2, U30.5, U30.6, U30.8
VIN30: C122.1, C124.1, JP211.2, JP217.2, L31.P$2, R151.2, U31.5, U31.6, U31.8
VIN31: C126.1, C128.1, JP218.2, JP224.2, L32.P$2, R156.2, U32.5, U32.6, U32.8
VIN32: C130.1, C132.1, JP225.2, JP231.2, L33.P$2, R161.2, U33.5, U33.6, U33.8
VIN33: C134.1, C136.1, JP232.2, JP238.2, L34.P$2, R166.2, U34.5, U34.6, U34.8
VIN34: C138.1, C140.1, JP239.2, JP245.2, L35.P$2, R171.2, U35.5, U35.6, U35.8
VIN35: C142.1, C144.1, JP246.2, JP252.2, L36.P$2, R176.2, U36.5, U36.6, U36.8
VIN36: C146.1, C148.1, JP253.2, JP259.2, L37.P$2, R181.2, U37.5, U37.6, U37.8
VIN37: C150.1, C152.1, JP260.2, JP266.2, L38.P$2, R186.2, U38.5, U38.6, U38.8
VIN38: C154.1, C156.1, JP267.2, JP273.2, L39.P$2, R191.2, U39.5, U39.6, U39.8
VIN39: C158.1, C160.1, JP274.2, JP280.2, L40.P$2, R196.2, U40.5, U40.6, U40.8
VIN40: C162.1, C164.1, JP281.2, JP287.2, L41.P$2, R201.2, U41.5, U41.6, U41.8
VIN41: C166.1, C168.1, JP288.2, JP294.2, L42.P$2, R206.2, U42.5, U42.6, U42.8
VIN42: C170.1, C172.1, JP295.2, JP301.2, L43.P$2, R211.2, U43.5, U43.6, U43.8
VIN43: C174.1, C176.1, JP302.2, JP308.2, L44.P$2, R216.2, U44.5, U44.6, U44.8
VIN44: C178.1, C180.1, JP309.2, JP315.2, L45.P$2, R221.2, U45.5, U45.6, U45.8
VIN45: C182.1, C184.1, JP316.2, JP322.2, L46.P$2, R226.2, U46.5, U46.6, U46.8
VIN46: C186.1, C188.1, JP323.2, JP329.2, L47.P$2, R231.2, U47.5, U47.6, U47.8
VIN47: C190.1, C192.1, JP330.2, JP336.2, L48.P$2, R236.2, U48.5, U48.6, U48.8
VIN48: C194.1, C196.1, JP337.2, JP343.2, L49.P$2, R241.2, U49.5, U49.6, U49.8
VIN49: C198.1, C200.1, JP344.2, JP350.2, L50.P$2, R246.2, U50.5, U50.6, U50.8
VIN50: C202.1, C204.1, JP351.2, JP357.2, L51.P$2, R251.2, U51.5, U51.6, U51.8
VIN51: C206.1, C208.1, JP358.2, JP364.2, L52.P$2, R256.2, U52.5, U52.6, U52.8
VIN52: C210.1, C212.1, JP365.2, JP371.2, L53.P$2, R261.2, U53.5, U53.6, U53.8
VIN53: C214.1, C216.1, JP372.2, JP378.2, L54.P$2, R266.2, U54.5, U54.6, U54.8
VIN54: C218.1, C220.1, JP379.2, JP385.2, L55.P$2, R271.2, U55.5, U55.6, U55.8
VIN55: C222.1, C224.1, JP386.2, JP392.2, L56.P$2, R276.2, U56.5, U56.6, U56.8
VIN56: C226.1, C228.1, JP393.2, JP399.2, L57.P$2, R281.2, U57.5, U57.6, U57.8
VIN57: C230.1, C232.1, JP400.2, JP406.2, L58.P$2, R286.2, U58.5, U58.6, U58.8
VIN58: C234.1, C236.1, JP407.2, JP413.2, L59.P$2, R291.2, U59.5, U59.6, U59.8
VIN59: C238.1, C240.1, JP414.2, JP420.2, L60.P$2, R296.2, U60.5, U60.6, U60.8
VIN60: C242.1, C244.1, JP421.2, JP427.2, L61.P$2, R301.2, U61.5, U61.6, U61.8
VIN61: C246.1, C248.1, JP428.2, JP434.2, L62.P$2, R306.2, U62.5, U62.6, U62.8
VIN62: C250.1, C252.1, JP435.2, JP441.2, L63.P$2, R311.2, U63.5, U63.6, U63.8
VIN63: C254.1, C256.1, JP442.2, JP448.2, L64.P$2, R316.2, U64.5, U64.6, U64.8

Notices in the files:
parts and their libraries:
SparkFun-Aesthetics: Licensing: CC v3.0 Share-Alike You are welcome to use this library for commercial purposes.
SparkFun-Aesthetics: Released under the Creative Commons Attribution Share-Alike 3.0 License
SparkFun-Aesthetics: http://creativecommons.org/licenses/by-sa/3.0
